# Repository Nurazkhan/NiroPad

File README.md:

# NiroPad
Simlple macropad to make your computer usage even faster.

I made this macropad with the help of hackClub. You can find useful references/examples in [Hackpad]([url](https://stardance.hackclub.com/missions/hackpad)) section.
## Features
* 128x32px for cool animations.
* 9 Cherry MX style Keys for best experience.
* 1 EC11 encoder to control with accuracy.
* Bright 18 RGB LEDS to make it GLOW. (9 for underglow, 4 under encoder, 4 near display, 1 under display)
* 3D printed perfect case with personal mentions.
* QMK Firmware

## CAD Model
CAD consists of a total of 3 parts: Case, Cover, Knob.
The case and the cover for it fit together with 4*M3 screws and heatset inserts.
The knob is attached to the encoder by friction.
The case has space for keys and displays, so it fits perfectly.

Made in OnShape. by Nurazkhan (me).

## PCB

Schematic was made in KiCad.

PCB routing was also made in KiCad Software. Footprints for keys were imported from recommended resources; you can also find [it]([url](https://github.com/sszczep/kicad-libraries)).

## Firmware Overview
The NiroPad Works on QMK firmware.
Main functions are:
* 9 keys for the number section. (My laptop doesn't have a separate keyboard section for numbers).
* Encoder to control volume.
* Dynamic LED control based on CAPS LOCK state.
* OLED showing the mode of the keyboard.
In the future, have to add more functions (changing modes from number sections to shortcuts, or media control, etc.
Also, planning to add animations to the OLED display.

## BOM
 * 9 Cherry MX style switches
 * 9 1N4148 diodes
 * 1 Custom PCB
 * 0.91 SSD1306 OLED display 128x32px
 * Xiao Speeed RPI2040 microcontroller
 * 3d printer enclosure (top and bottom) and knob for encoder
 * EC11 Encoder
 * 4 M3*16mm screws
 * 4 M3*5m*4mm heatset inserts

The process of designing and creation you can see in the journals folder.

Thank you!
#hackClub

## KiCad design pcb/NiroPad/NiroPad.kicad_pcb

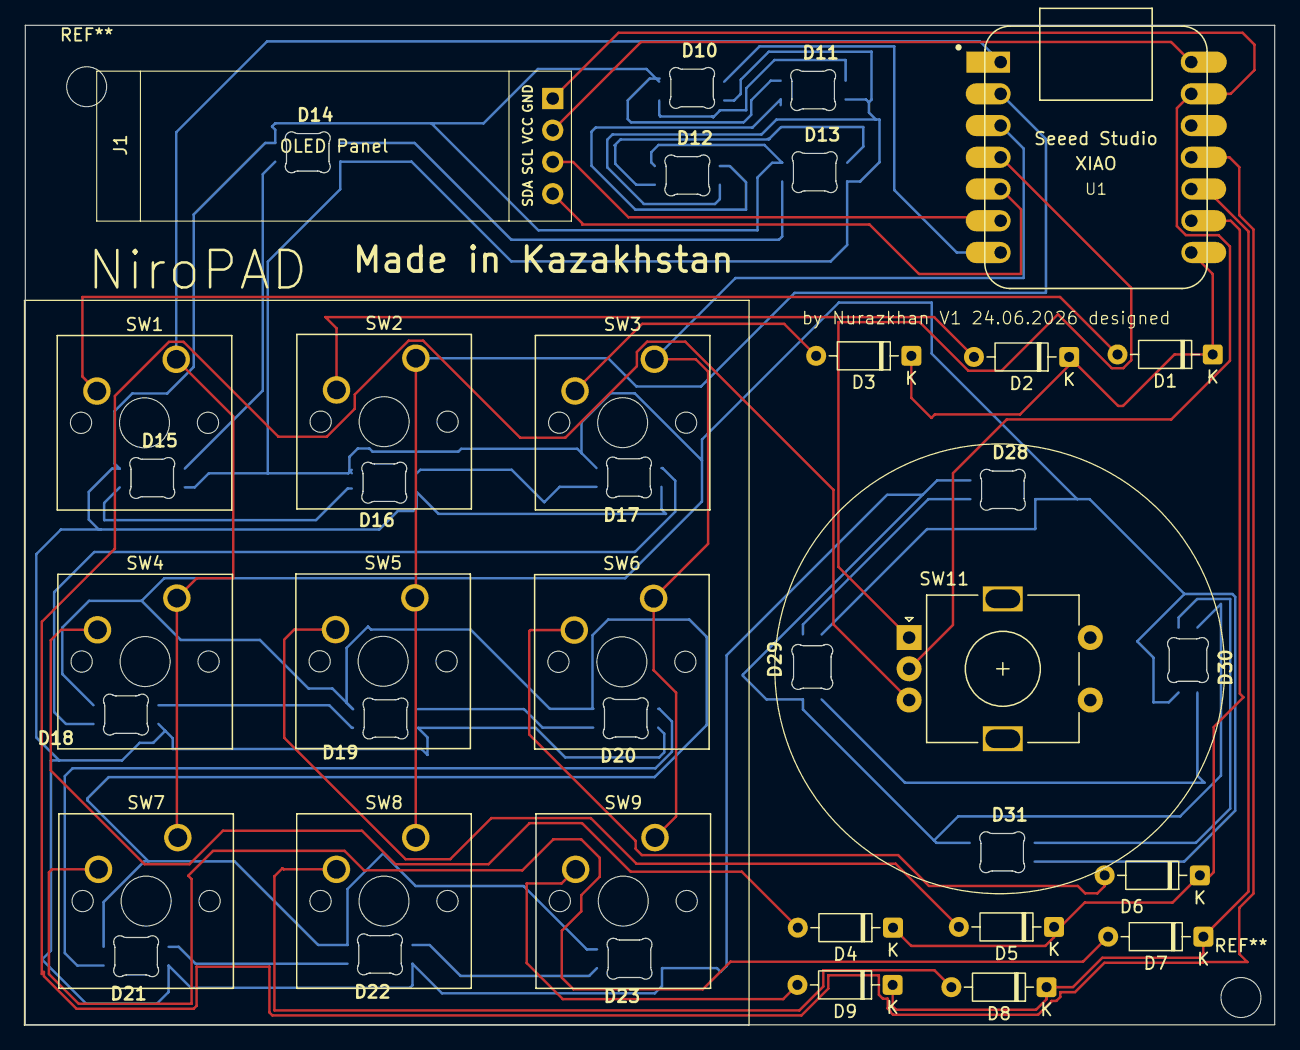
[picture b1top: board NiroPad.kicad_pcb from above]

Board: 2 copper layers, 99.9 x 80.0 mm, 39 parts (0 on the bottom side), 40 nets.

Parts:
D1, D2, D3, D4, D5, D6, D7, D8, D9: 1N4148; D_DO-35_SOD27_P7.62mm_Horizontal
D10, D11, D12, D13, D14, D15, D16, D17, D18, D19, D20, D21, D22, D23, D28, D29, D30, D31: SK6812MINI-E; SK6812MINI-E_fixed
J1: OLED display; SSD1306-0.91-OLED-4pin-128x32
SW1, SW2, SW3, SW4, SW5, SW6, SW7, SW8, SW9: SW_Push; footprint
SW11: RotaryEncoder_Switch; RotaryEncoder_Alps_EC11E-Switch_Vertical_H20mm
U1: MOUDLE-SEEEDUINO-XIAO; XIAO-Generic-Hybrid-14P-2.54-21X17.8MM

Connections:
COL1: SW1.1, SW4.1, SW7.1, U1.1 (PA02_A0_D0)
COL2: SW2.1, SW5.1, SW8.1, U1.2 (PA4_A1_D1)
COL3: SW3.1, SW6.1, SW9.1, U1.3 (PA10_A2_D2)
ENC_A: SW11.A, U1.4 (PA11_A3_D3)
ENC_B: SW11.B, U1.11 (PA6_A10_D10_MOSI)
GND: J1.1, SW11.C, U1.13 (GND)
LED: D10.4 (DIN), U1.7 (PB08_A6_D6_TX)
unnamed: D1.2 (A), SW1.2
unnamed: D2.2 (A), SW2.2
unnamed: D3.2 (A), SW3.2
unnamed: D4.2 (A), SW4.2
unnamed: D5.2 (A), SW5.2
unnamed: D6.2 (A), SW6.2
unnamed: D7.2 (A), SW7.2
unnamed: D8.2 (A), SW8.2
unnamed: D9.2 (A), SW9.2
unnamed: D10.2 (DOUT), D11.4 (DIN)
unnamed: D10.1 (VDD), D11.1 (VDD), D12.1 (VDD), D13.1 (VDD), D14.1 (VDD), D15.1 (VDD), D16.1 (VDD), D17.1 (VDD), D18.1 (VDD), D19.1 (VDD), D20.1 (VDD), D21.1 (VDD), D22.1 (VDD), D23.1 (VDD), D28.1 (VDD), D29.1 (VDD), D30.1 (VDD), D31.1 (VDD)
unnamed: D10.3 (VSS), D11.3 (VSS), D12.3 (VSS), D13.3 (VSS), D14.3 (VSS), D15.3 (VSS), D16.3 (VSS), D17.3 (VSS), D18.3 (VSS), D19.3 (VSS), D20.3 (VSS), D21.3 (VSS), D22.3 (VSS), D23.3 (VSS), D28.3 (VSS), D29.3 (VSS), D30.3 (VSS), D31.3 (VSS)
unnamed: D11.2 (DOUT), D12.4 (DIN)
unnamed: D12.2 (DOUT), D13.4 (DIN)
unnamed: D13.2 (DOUT), D14.4 (DIN)
unnamed: D14.2 (DOUT), D15.4 (DIN)
unnamed: D15.2 (DOUT), D16.4 (DIN)
unnamed: D16.2 (DOUT), D17.4 (DIN)
unnamed: D17.2 (DOUT), D18.4 (DIN)
unnamed: D18.2 (DOUT), D19.4 (DIN)
unnamed: D19.2 (DOUT), D20.4 (DIN)
unnamed: D20.2 (DOUT), D21.4 (DIN)
unnamed: D21.2 (DOUT), D22.4 (DIN)
unnamed: D22.2 (DOUT), D23.4 (DIN)
unnamed: D28.2 (DOUT), D29.4 (DIN)
unnamed: D29.2 (DOUT), D30.4 (DIN)
unnamed: D30.2 (DOUT), D31.4 (DIN)
ROW1: D1.1 (K), D2.1 (K), D3.1 (K), U1.8 (PB09_A7_D7_RX)
ROW2: D4.1 (K), D5.1 (K), D6.1 (K), U1.9 (PA7_A8_D8_SCK)
ROW3: D7.1 (K), D8.1 (K), D9.1 (K), U1.10 (PA5_A9_D9_MISO)
SCL: J1.3, U1.6 (PA9_A5_D5_SCL)
SDA: J1.4, U1.5 (PA8_A4_D4_SDA)
VCC: J1.2, U1.14 (5V)

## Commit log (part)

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2026-06-25 V0.6 Scheme + PCB + board 3D
2026-06-26 PCB+3d+QMK - everything done?
2026-06-26 ReadmeChanged
